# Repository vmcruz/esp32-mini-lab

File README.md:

# ESP32-Mini-Lab

A compact, portable ESP32-C3 development device built from a custom-designed PCB and a 3D-printed enclosure. It combines a USB-C-powered ESP32-C3-MINI-1, a microSD card reader, an OLED display, and a 5-way D-pad into a small, self-contained hardware platform for experimentation and development.

The project was designed from scratch, including the PCB layout, firmware, and enclosure. It serves as a hands-on platform for exploring embedded development, hardware integration, and portable ESP32 applications.

## Features

- **ESP32-C3-MINI-1** microcontroller.
- **USB-C power and connectivity**, with no internal battery required.
- **0.96-inch I²C OLED display** for status information and interface output.
- **MicroSD card reader** for external storage.
- **5-way D-pad** for directional input and selection.
- **Custom-designed PCB**, manufactured and assembled by PCBWay.
- **Custom 3D-printed enclosure**, designed to house the PCB and its components.
- **PlatformIO + Arduino framework** for firmware development.

## Project Status

**V1 — Completed and functional.**

The first revision has been fabricated, assembled, enclosed, and tested. The core hardware and firmware are operational (see [CHANGELOG.md](CHANGELOG.md)).

A V2 revision is planned to refine the enclosure's ergonomics, cable clearance, screw mounting, and closure mechanism based on real-world testing (see [TODO.md](TODO.md)).

## Goals

- Build a compact, portable platform for ESP32 experimentation.
- Integrate common embedded-development components into a single device.
- Explore custom PCB design, firmware development, and 3D-printed mechanical design.
- Iterate through hardware revisions based on practical use and testing.

## Power

The device is powered through USB-C and is designed to operate from a standard 5 V USB power source. Compatible smartphones may also be used as a power source, potentially eliminating the need to carry a separate power bank.

## Repository Structure

| Directory / File      | Description                                                                                                                        |
| --------------------- | ---------------------------------------------------------------------------------------------------------------------------------- |
| `Firmware/`           | Complete firmware source code and development configuration.                                                                       |
| `Hardware/Enclosure/` | 3D-printable enclosure model.                                                                                                      |
| `Hardware/KiCad/`     | Complete KiCad project, including schematics and PCB design files.                                                                 |
| `Hardware/PCBWay/`    | PCB manufacturing and assembly files, including Gerbers, drill files, bill of materials (BOM), and pick-and-place positions (POS). |
| `LICENSES/`           | License texts applicable to the project components.                                                                                |

## License

ESP32-Mini-Lab uses different open-source licenses for its components:

- **Firmware:** [MIT License](LICENSES/MIT.txt)
- **PCB and schematics:** [CERN-OHL-P-2.0](LICENSES/CERN-OHL-P-2.0.txt)
- **3D enclosure models:** [CERN-OHL-P-2.0](LICENSES/CERN-OHL-P-2.0.txt)

Please refer to the applicable license for each component.

## Acknowledgements

Special thanks to **[PajoPCB](https://www.youtube.com/@PajoPCB)** for the tutorial that inspired the PCB design of ESP32-Mini-Lab.

Original tutorial: **[**KiCad 9 ESP32-C3 Mini PCB Design | Full Schematic Walkthrough**](https://www.youtube.com/watch?v=-iZbwzr0dS8)** (watch on youtube)

Thanks for sharing your knowledge and making hardware design more accessible to the maker community.

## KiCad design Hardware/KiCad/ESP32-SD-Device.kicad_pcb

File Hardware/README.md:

## PCB

## GPIO Reference

The following table maps the ESP32-C3 GPIOs to their corresponding signal names in the hardware design.

| GPIO   | Signal |
| ------ | ------ |
| GPIO0  | -      |
| GPIO1  | -      |
| GPIO2  | HIGH\* |
| GPIO3  | -      |
| GPIO4  | -      |
| GPIO5  | CS     |
| GPIO6  | MOSI   |
| GPIO7  | MISO   |
| GPIO10 | SCK    |
| GPIO18 | USB D- |
| GPIO19 | USB D+ |
| GPIO20 | SDA    |
| GPIO21 | SCL    |

\*Notice: GPIO2 is connected to 3.3 V through an external 10 kΩ pull-up resistor (R9), which can be removed if needed for a different GPIO configuration.

**Note:** Signal names identify the nets in the hardware design; they do not restrict how the GPIOs may be used in other projects. The CS, MOSI, MISO, and SCK signals are not individually labeled on the PCB silkscreen.

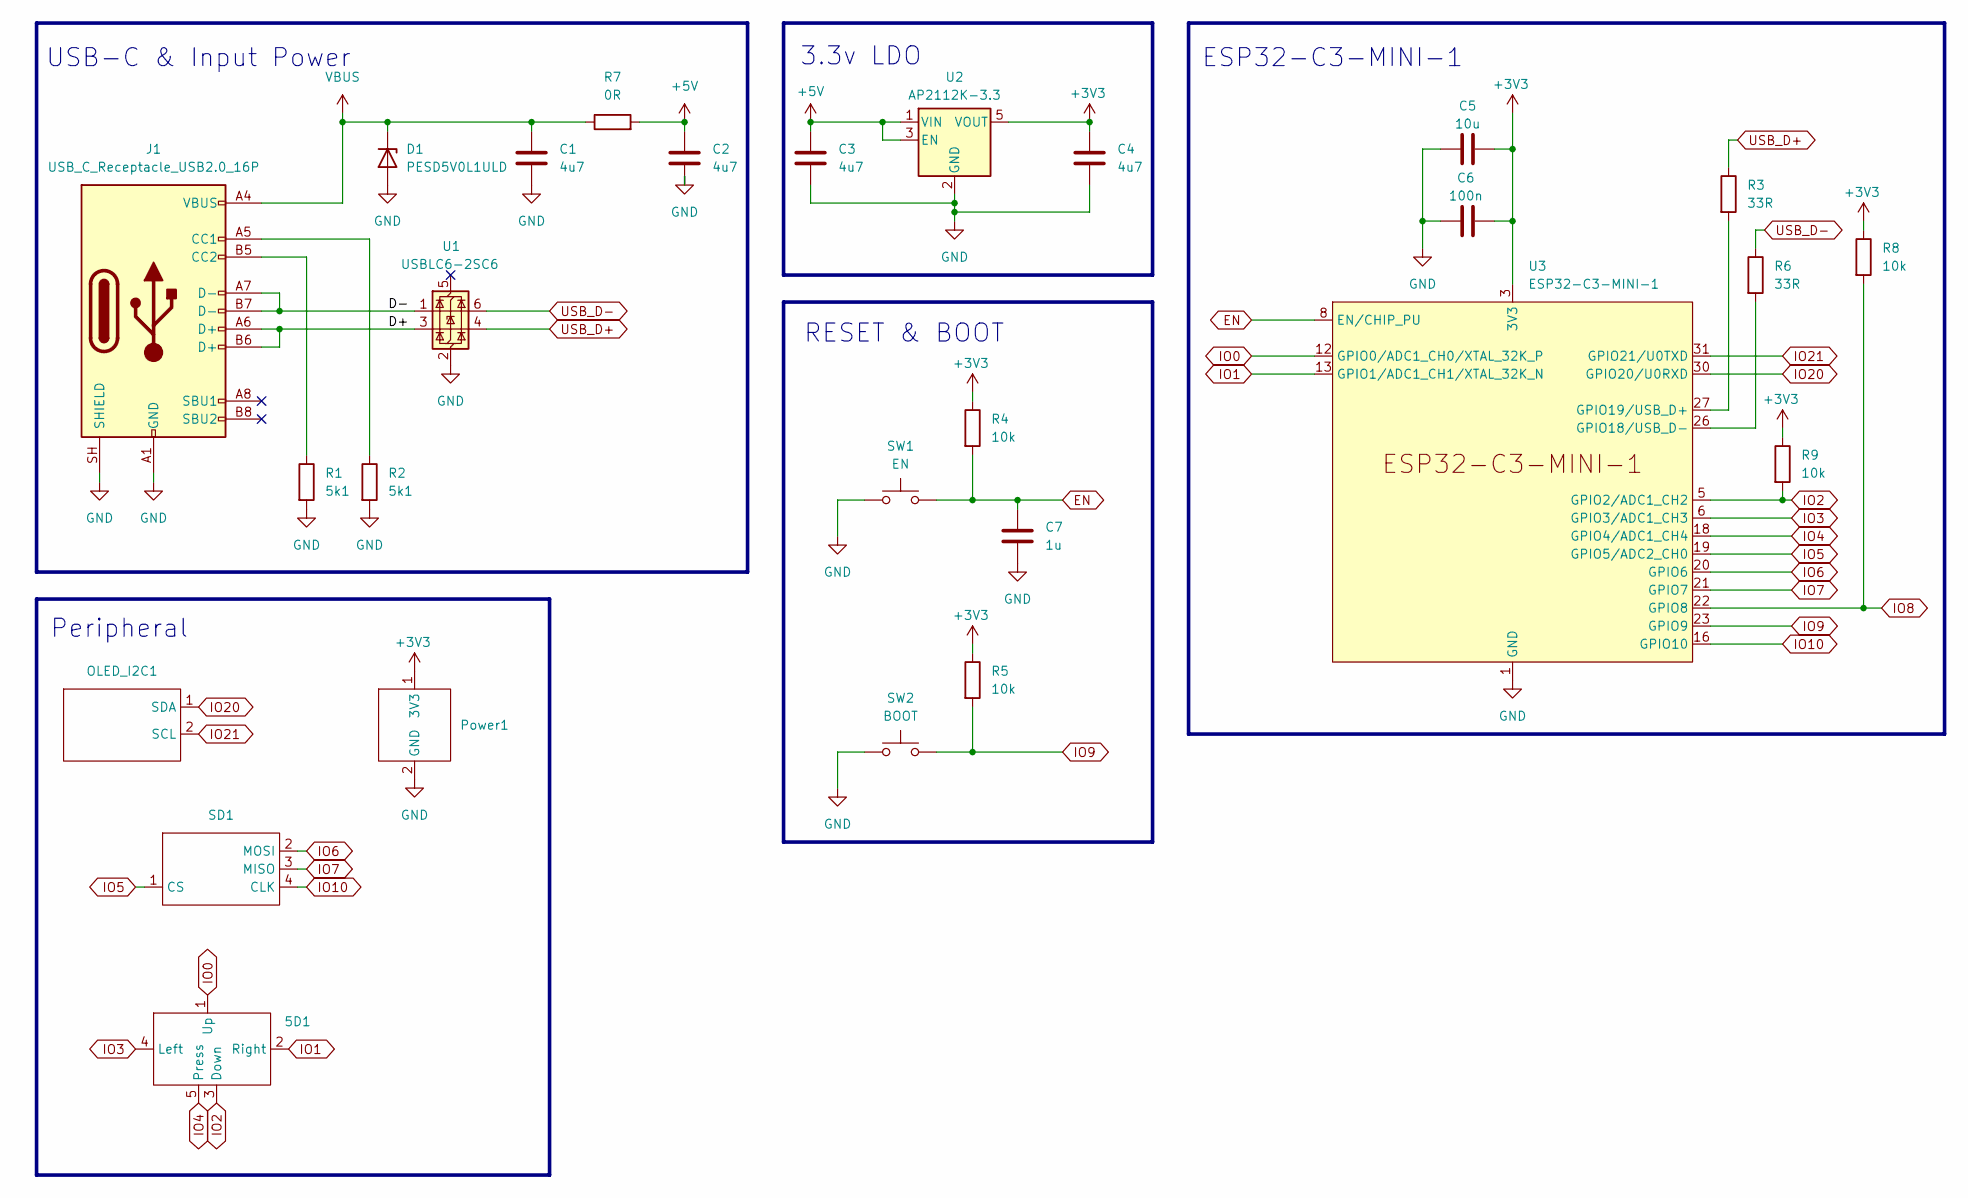
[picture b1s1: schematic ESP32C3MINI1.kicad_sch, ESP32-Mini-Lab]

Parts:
5D1: 5D_Interface
C1, C2, C3, C4: 4u7; C_0805_2012Metric
C5: 10u; C_0805_2012Metric
C6: 100n; C_01005_0402Metric
C7: 1u; C_0805_2012Metric
D1: PESD5V0L1ULD; D_SOD-882D
J1: USB_C_Receptacle_USB2.0_16P; USB_C_Receptacle_GCT_USB4105-xx-A_16P_TopMnt_Horizontal
OLED_I2C1: OLED_Interface
Power1: Power_Interface
R1, R2: 5k1; R_0402_1005Metric
R3, R6: 33R; R_0805_2012Metric
R4, R5, R8, R9: 10k; R_0402_1005Metric
R7: 0R; R_0805_2012Metric
SD1: SD_Interface
SW1: EN; SW_SPST_B3U-1000P
SW2: BOOT; SW_SPST_B3U-1000P
U1: USBLC6-2SC6; SOT-23-6
U2: AP2112K-3.3; SOT-23-5
U3: ESP32-C3-MINI-1

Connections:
+3V3: C4.1, C5.2, C6.2, Power1.1 (3V3), R4.1, R5.1, R8.1, R9.1, U2.5 (VOUT), U3.3 (3V3)
+5V: C2.1, C3.1, R7.2, U2.1 (VIN), U2.3 (EN)
/ESP32-C3-MINI-1/D+: J1.A6 (D+), J1.B6 (D+), U1.3 (I/O2)
/ESP32-C3-MINI-1/D-: J1.A7 (D-), J1.B7 (D-), U1.1 (I/O1)
EN: C7.1, R4.2, SW1.2, U3.8 (EN/CHIP_PU)
GND: C1.2, C2.2, C3.2, C4.2, C5.1, C6.1, C7.2, D1.2 (A), J1.A1 (GND), J1.A12 (GND), J1.B1 (GND), J1.B12 (GND), J1.SH (SHIELD), Power1.2 (GND), R1.2, R2.2, SW1.1, SW2.1, U1.2 (GND), U2.2 (GND), U3.1 (GND), U3.2 (GND), U3.11 (GND), U3.14 (GND), U3.36 (GND), U3.37 (GND), U3.38 (GND), U3.39 (GND), U3.40 (GND), U3.41 (GND), U3.42 (GND), U3.43 (GND), U3.44 (GND), U3.45 (GND), U3.46 (GND), U3.47 (GND), U3.48 (GND), U3.49 (GND), U3.50 (GND), U3.51 (GND), U3.52 (GND), U3.53 (GND)
IO0: 5D1.1 (Up), U3.12 (GPIO0/ADC1_CH0/XTAL_32K_P)
IO1: 5D1.2 (Right), U3.13 (GPIO1/ADC1_CH1/XTAL_32K_N)
IO2: 5D1.3 (Down), R9.2, U3.5 (GPIO2/ADC1_CH2)
IO3: 5D1.4 (Left), U3.6 (GPIO3/ADC1_CH3)
IO4: 5D1.5 (Press), U3.18 (GPIO4/ADC1_CH4)
IO5: SD1.1 (CS), U3.19 (GPIO5/ADC2_CH0)
IO6: SD1.2 (MOSI), U3.20 (GPIO6)
IO7: SD1.3 (MISO), U3.21 (GPIO7)
IO8: R8.2, U3.22 (GPIO8)
IO9: R5.2, SW2.2, U3.23 (GPIO9)
IO10: SD1.4 (CLK), U3.16 (GPIO10)
IO20: OLED_I2C1.1 (SDA), U3.30 (GPIO20/U0RXD)
IO21: OLED_I2C1.2 (SCL), U3.31 (GPIO21/U0TXD)
unnamed: J1.A5 (CC1), R2.1
unnamed: J1.B5 (CC2), R1.1
unnamed: R6.2, U3.26 (GPIO18/USB_D-)
unnamed: R3.2, U3.27 (GPIO19/USB_D+)
USB_D+: R3.1, U1.4 (I/O2)
USB_D-: R6.1, U1.6 (I/O1)
VBUS: C1.1, D1.1 (K), J1.A4 (VBUS), J1.A9 (VBUS), J1.B4 (VBUS), J1.B9 (VBUS), R7.1

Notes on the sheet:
3.3v LDO
Peripheral
USB-C & Input Power
ESP32-C3-MINI-1
RESET & BOOT

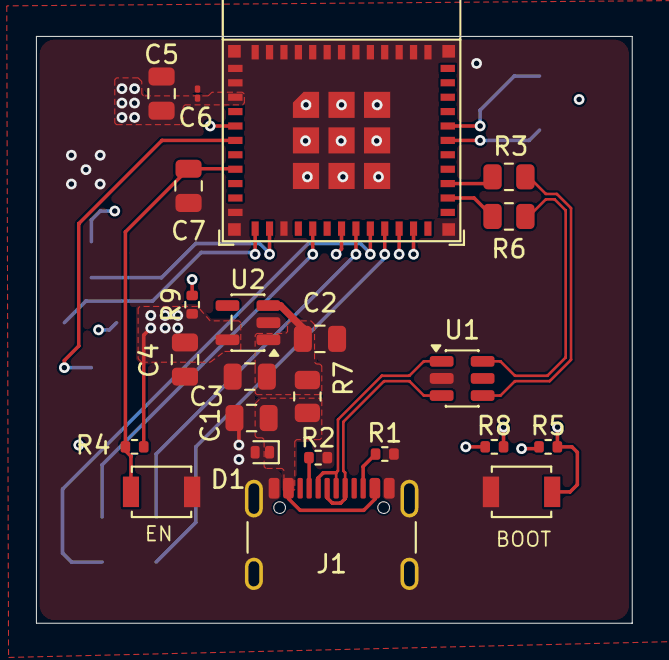
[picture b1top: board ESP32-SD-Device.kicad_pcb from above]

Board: 4 copper layers, 33.1 x 32.6 mm, 27 parts (0 on the bottom side), 26 nets.

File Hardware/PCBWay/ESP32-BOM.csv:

Designator,Qty,Manufacturer,Mfg Part #,Description / Value,Package/Footprint,Type,Your Instructions / Notes
"C1,C2,C3,C4",4,Murata Electronics,GRM21BR71A475KE51K,"4.7uF, 10V, X7R, ±10%",0805 (2012 Metric),SMD,
C5,1,Murata Electronics,GRM21BR61A106KE19K,"10uF, 10V, X5R, ±10%",0805 (2012 Metric),SMD,
C6,1,Murata Electronics,GRM022R60J104KE15L,"100nF, 6.3V, X5R, ±10%",01005 (0402 Metric),SMD,
C7,1,Murata Electronics,GRM21BR71A105KA01K,"1uF, 10V, X7R, ±10%",0805 (2012 Metric),SMD,
D1,1,Nexperia,"PESD5V0L1ULD,315",5V TVS ESD protection diode,SOD-882D / DFN1006D-2,SMD,
J1,1,GCT,USB4105-GF-A,"USB Type-C receptacle, USB 2.0, 16P","USB4105 series, top-mount horizontal",SMD,
"R1,R2",2,YAGEO,RC0402FR-075K1L,"5.1kOhm, 1%, 1/16W",0402 (1005 Metric),SMD,
"R3,R6",2,YAGEO,RC0805FR-0733RL,"33Ohm, 1%, 1/8W",0805 (2012 Metric),SMD,
"R4,R5,R8,R9",4,YAGEO,RC0402FR-0710KL,"10kOhm, 1%, 1/16W",0402 (1005 Metric),SMD,
R7,1,YAGEO,RC0805FR-070RL,0Ohm jumper,0805 (2012 Metric),SMD,
"SW1,SW2",2,OMRON,B3U-1000P,"Tactile switch, SPST-NO, top actuated",3.0 x 2.5mm SMD,SMD,
U1,1,STMicroelectronics,USBLC6-2SC6,"USB 2.0 ESD protection, 2 data lines",SOT-23-6,SMD,
U2,1,Diodes Incorporated,AP2112K-3.3TRG1,3.3V 600mA LDO,SOT-23-5,SMD,
U3,1,Espressif Systems,ESP32-C3-MINI-1-N4X,"ESP32-C3 module, integrated 4MB flash, PCB antenna",ESP32-C3-MINI-1,SMD,
